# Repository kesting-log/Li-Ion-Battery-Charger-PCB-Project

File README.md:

# Lithium-Ion Battery Charger
  Rendered 3D view of the PCB Layout:

  Video of the Fabricated PCB Charging a Device:

  https://github.com/user-attachments/assets/34a2994c-56c9-4d0d-9e32-f9736337a1a2

## Overview
This is a portable, self-iniated power electronics project for a custom PCB in KiCad. The module charges a low-voltage (3.7V nominal) lithium-ion battery from a DC/DC voltage regulator and discharges to an 
external device via a USB-C connector.

## System-Level Block Diagram

The voltage regulator charging the Lithium-Ion battery regulates a 5V DC input (via Micro USB-B) to the maximum voltage of the battery (4.2V). As the battery is used 
to charge an external device, the voltage decreases until it reaches 3V, where it dies and can no longer supply the external device. When the battery is being used to charge an external device, the voltage 
is increased back to 5V via an output regulated boost converter. The output voltage is determined by two feedback resistors that make up a voltage divider, where the voltage across the lower resistor 
(called the feedback voltage) is fed to a comparator within the IC. The feedback voltage is internally set to 1.24 V, allowing the output voltage to be set by the following equation:

Vout = Vref * (Rtop / Rbot + 1)

Where:
Vref = 1.24V
Rbot ≤ 5kΩ

In this application, Rtop = 9.1kΩ and Rbot = 3kΩ making the regulated output voltage of the boost converter Vout ≈ 5V.

The USB-C connector in the system has a 6-pin (power only) configuration and uses two pull-up 56kΩ resistors on the CC pins to charge the external device at default power (5V @ 500mA) - using the USB 2.0 protocol. The CC pin voltage is also used to drive PMOS MOSFET gates. When the external device is not connected, the CC pin voltages are pulled up to 5V, preventing the PMOS from conducting to illuminate the LED. When an external device is connected
the PMOS gate voltage is significacntly less than at the source of the PMOS, turning on the MOSFET and thus illuminating the LED. See the system schematic and PCB below for further reference.

## PCB Design
### KiCad Schematic
- The KiCad schematic shows the electrical connections of the circuit.
  - 

### KiCad PCB
- The KiCad PCB shows the physical connections and overall routing of traces in the circuit.
  - 

### Bill of Materials (BOM)
-  Below is the Bill of Materials, or the needed parts for the project:
  - 

## File Structure
- `/BOM`: Contains Bill of Materials for the project.
- `/Diagrams`: Contains system-level block diagram of the project.
- `/KiCad Project`: KiCad project file, including schematics and PCB layouts.
- `/PCB`: Contains KiCad PCB file, screenshot of the KiCad PCB design, video of the fabricated PCB, and the 3D view of the PCB.
- `/Schematic`: Contains KiCad schematic file and a screenshot of the KiCad Schematic design.

## How to Use
1. Open the KiCad files from the `/PCB` and `/Schematic` folders to review the PCB layout and schematic.
2. Open the KiCad project from the `/KiCad Project` folder to download the whole project including the PCB and schematic.
3. For the system design, check out the block diagram in `/Diagrams`.
4. For the Bill of Materials, navigate to the `/BOM` folder to see the specific components used in the project

## License

This hardware design is licensed under the **CERN Open Hardware License v2 - Strongly Reciprocal (CERN-OHL-S)**. You are free to use, modify, and share this project, as long as you distribute any derived works under the same license.

For more details, see the [LICENSE](./LICENSE) file.

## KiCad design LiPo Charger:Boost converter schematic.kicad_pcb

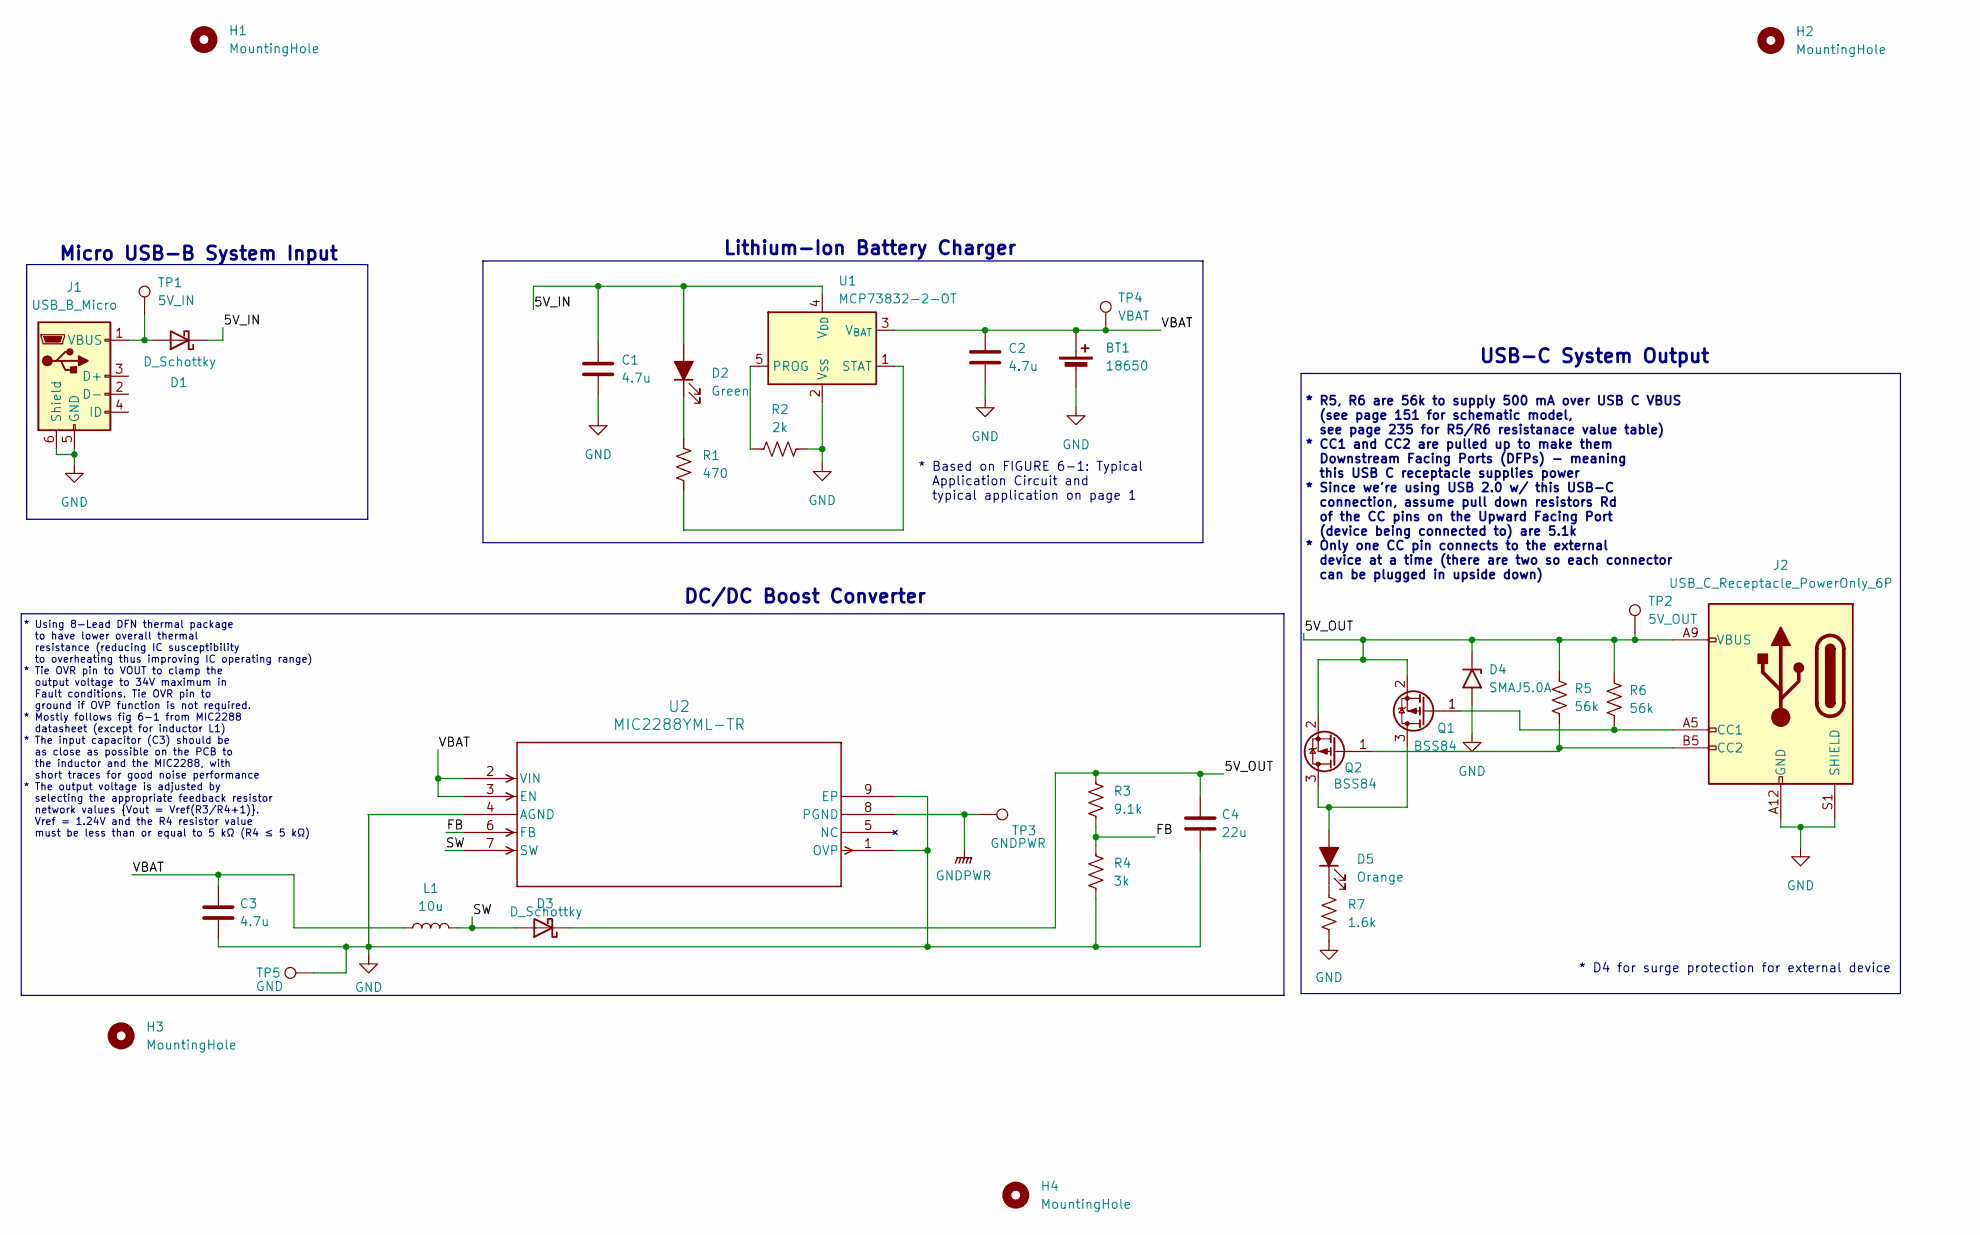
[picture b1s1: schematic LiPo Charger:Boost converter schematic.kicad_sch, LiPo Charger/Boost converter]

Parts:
BT1: 18650; BatteryHolder_Keystone_1042_1x18650; Digikey Part Number 36-1042-ND; 1568-1488-ND
C1, C2, C3: 4.7u; C_1812_4532Metric_Pad1.57x3.40mm_HandSolder; Digikey Part Number 399-14738-1-ND
C4: 22u; C_1206_3216Metric_Pad1.33x1.80mm_HandSolder; Digikey Part Number 478-KGM31HR50J226KUCT-ND
D1, D3: D_Schottky; D_1206_3216Metric_Pad1.42x1.75mm_HandSolder; Digikey Part Number 478-7806-1-ND
D2: Green; LED_1206_3216Metric_Pad1.42x1.75mm_HandSolder; Digikey Part Number 1080-1419-1-ND
D4: SMAJ5.0A; D_SMA; Digikey Part Number SMAJ5.0ALFCT-ND
D5: Orange; LED_1206_3216Metric_Pad1.42x1.75mm_HandSolder; Digikey Part Number 754-1941-1-ND
H1, H2, H3, H4: MountingHole; MountingHole_3mm
J1: USB_B_Micro; USB_Micro-B_Amphenol_10104110_Horizontal; Digikey Part Number 609-4052-1-ND
J2: USB_C_Receptacle_PowerOnly_6P; USB_C_Receptacle_GCT_USB4135-GF-A_6P_TopMnt_Horizontal; Digikey Part Number 2073-USB4135-GF-ACT-ND
L1: 10u; L_Abracon_ASPI-4030S; Digikey Part Number 535-12314-1-ND
Q1, Q2: BSS84; SOT-23; Digikey Part Number 1727-2931-1-ND
R1: 470; R_1206_3216Metric_Pad1.30x1.75mm_HandSolder; Digikey Part Number A106077CT-ND
R2: 2k; R_1206_3216Metric_Pad1.30x1.75mm_HandSolder; Digikey Part Number 311-2.00KFRCT-ND
R3: 9.1k; R_1206_3216Metric_Pad1.30x1.75mm_HandSolder; Digikey Part Number 2019-RK73H2BTTD9101FCT-ND
R4: 3k; R_1206_3216Metric_Pad1.30x1.75mm_HandSolder; Digikey Part Number 311-3.00KFRCT-ND
R5, R6: 56k; R_1206_3216Metric_Pad1.30x1.75mm_HandSolder; Digikey Part Number RMCF1206JT56K0CT-ND
R7: 1.6k; R_1206_3216Metric_Pad1.30x1.75mm_HandSolder; Digikey Part Number 311-1.60KFRCT-ND
TP1: 5V_IN; TestPoint_THTPad_D2.5mm_Drill1.2mm; Digikey Part Number 36-5001-ND
TP2: 5V_OUT; TestPoint_THTPad_D2.5mm_Drill1.2mm; Digikey Part Number 36-5001-ND
TP3: GNDPWR; TestPoint_THTPad_D2.5mm_Drill1.2mm; Digikey Part Number 36-5001-ND
TP4: VBAT; TestPoint_THTPad_D2.5mm_Drill1.2mm; Digikey Part Number 36-5001-ND
TP5: GND; TestPoint_THTPad_D2.5mm_Drill1.2mm; Digikey Part Number 36-5001-ND
U1: MCP73832-2-OT; SOT-23-5_HandSoldering; Digikey Part Number MCP73832T-2DCI/OTCT-ND
U2: MIC2288YML-TR; MLF-8_ML_MCH; Digikey Part Number 576-1075-1-ND

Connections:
/5V_IN: C1.1, D1.1 (K), D2.2 (A), U1.4 (V_{DD})
/5V_OUT: C4.1, D3.1 (K), D4.1 (A1), J2.A9 (VBUS), J2.B9 (VBUS), Q1.2 (S), Q2.2 (S), R3.1, R5.1, R6.1, TP2.1
/FB: R3.2, R4.1, U2.6 (FB)
/SW: D3.2 (A), L1.2, U2.7 (SW)
/VBAT: BT1.1 (+), C2.1, C3.1, L1.1, TP4.1, U1.3 (V_{BAT}), U2.2 (VIN), U2.3 (EN)
GND: BT1.2 (-), C1.2, C2.2, C3.2, C4.2, D4.2 (A2), J1.5 (GND), J1.6 (Shield), J2.A12 (GND), J2.B12 (GND), J2.S1 (SHIELD), R2.2, R4.2, R7.2, TP5.1, U1.2 (V_{SS}), U2.1 (OVP), U2.4 (AGND), U2.9 (EP)
GNDPWR: TP3.1, U2.8 (PGND)
unnamed: D1.2 (A), J1.1 (VBUS), TP1.1
unnamed: D2.1 (K), R1.1
unnamed: D5.2 (A), Q1.3 (D), Q2.3 (D)
unnamed: D5.1 (K), R7.1
unnamed: J2.A5 (CC1), Q1.1 (G), R6.2
unnamed: J2.B5 (CC2), Q2.1 (G), R5.2
unnamed: R2.1, U1.5 (PROG)
unnamed: R1.2, U1.1 (STAT)

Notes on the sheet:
USB-C System Output
* R5, R6 are 56k to supply 500 mA over USB C VBUS (see page 151 for schematic model, see page 235 for R5/R6 resistanace value table) * CC1 and CC2 are pulled up to make them Downstream Facing Ports (DFPs) - meaning this USB C receptacle supplies power * Since we're using USB 2.0 w/ this USB-C conne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
Lithium-Ion Battery Charger
* Using 8-Lead DFN thermal package to have lower overall thermal resistance (reducing IC susceptibility to overheating thus improving IC operating range) * Tie OVR pin to VOUT to clamp the output voltage to 34V maximum in Fault conditions. Tie OVR pin to ground if OVP function is not required. * Mo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
* Based on FIGURE 6-1: Typical Application Circuit and typical application on page 1
DC/DC Boost Converter
* D4 for surge protection for external device
Micro USB-B System Input

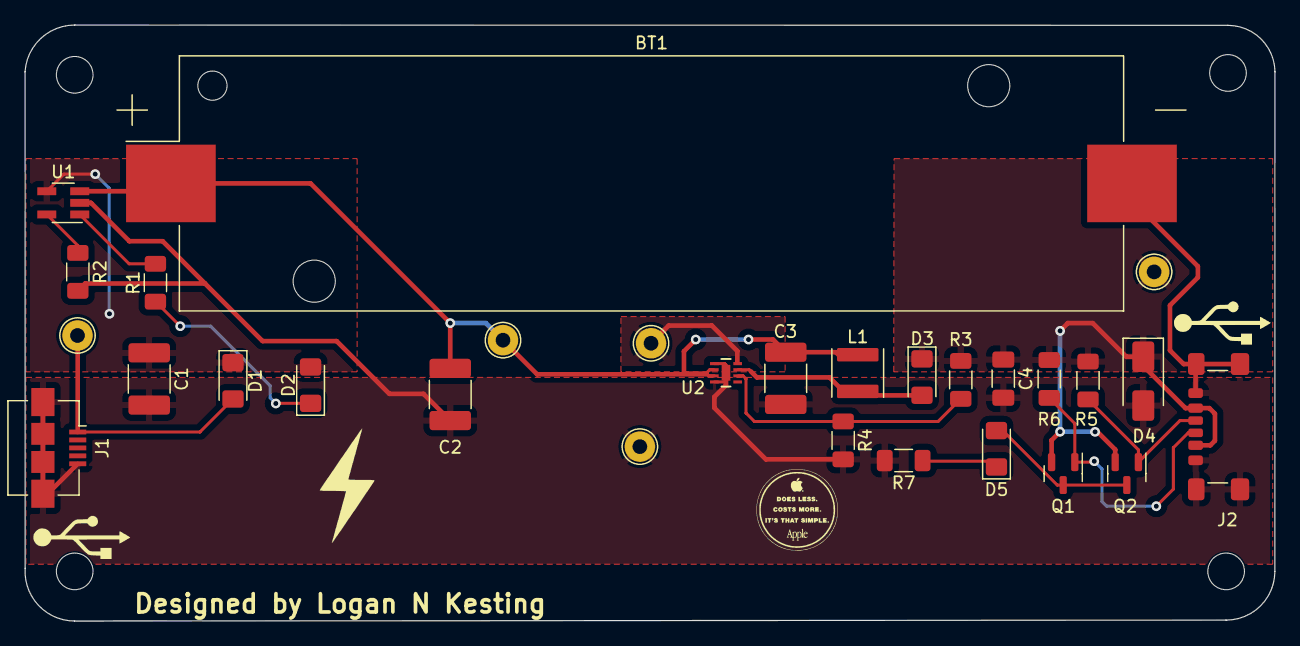
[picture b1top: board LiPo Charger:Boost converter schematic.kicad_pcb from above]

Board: 2 copper layers, 102.3 x 48.8 mm, 33 parts (0 on the bottom side), 15 nets.

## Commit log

2024-10-09 Add files via upload
    Lithium-Ion Battery Charger KiCad Schematic
2024-10-09 Add files via upload
    Lithium-Ion Battery Charger KiCad PCB
2024-10-09 Create KiCad Files
2024-10-10 Create LICENSE
2025-06-04 Create Final Product
2025-06-04 Create Fabbed PCB
2025-06-04 Create PCB
2025-06-04 Create Fabricated PCB Video
